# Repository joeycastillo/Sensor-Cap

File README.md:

# The Sensor Cap

Boards with a 9-pin JST-SH connector for sensors, inspired by the [Adafruit Monster M4SK](https://www.adafruit.com/product/4343).

This started as a project to mount a temperature sensor on my forehead for continuous temperature monitoring. It's ended up being something broader in nature. Call it a general platform for wearable tech and citizen science, maybe? Also as a side note, I'm hunting for a new name for this project since it's more than a hat now.

You might ask: why another board? Why not just use a Feather? The answer is that while Feathers are AWESOME, tiny and portable and battery-operated, the main method for attaching wings (board to board pin headers) makes the solution a little more bulky than I would like for something like a hat or a watch. Standards like STEMMA and STEMMA-QT address that somewhat, but STEMMA ports only break out one signal, and STEMMA-QT only supports I²C devices.

This standard breaks out three to five analog signals and I²C. It's far fewer than a Feather header offers, but still, I sense, enough to do some useful stuff! In addition, the connector is small enough that you can keep your sensor boards very small, which is great for wearables, and makes it really cheap to prototype a tiny board at OSH Park.

## Scope

This document describes a connector with a baseline of functionality for designing small PCB's with sensors. Before diving in, some nomenclature: a **main board** hosts whatever microcontroller or processor is driving gadgets on a **sensor board**.

The intent is for different main boards with different goals (i.e low power, machine learning, compact form factor, IOT) to implement this baseline level of functionality on a standard pinout, so that sensor boards know where to expect which functions.

It is not designed for daisy-chaining like STEMMA or Qwiic. When you design your sensor board, you can make use of all of the available pins, secure in the knowledge that you don't need to plan on sharing (except in the case of the I²C pins but, y'know, you can play nice with others there).

Main boards can offer additional functionality on some pins, and this document includes guidelines about what that pinout should look like. This should maximize the amount of compatibility across boards. Still, fundamentally, I imagine the user will either be able to make their sensor package work with the baseline of the spec, or they will choose a main board that works for their project and design their sensor package to match its abilities and constraints.

## Main Board

If possible, all pins should be analog inputs; if not, make sure pins 5, 6 and 9 (A2, A1 and A0) are analog capable. If you have a DAC available, put it on pin 9, A0. All IO pins are 3.3 volt logic.

### Main Board Pinout

1. Power to the sensor board, nominally 3.3 volts, can be lower but no higher.
2. Ground. 
3. Digital input or output D1. (Optional: analog input, or SPI main in/secondary out)
4. Digital input or output D0. (Optional: analog input)
5. Analog input A2 or digital in/out. (Optional: SPI main out/secondary in)
6. Analog input A1 or digital in/out. (Optional: SPI clock)
7. I²C data.
8. I²C clock.
9. Analog input A0 or digital in/out. (Optional: Analog output)

Why are some pins designated as analog and some pins designated as either digital or analog? Because if you’re in a situation where you have a limited number of pins available, this lets you know to prioritize putting your analog inputs on pins 5, 6 and 9, and your analog output (if available) on pin 9.

The main board **must** provide I²C pull-up resistors on the SCL and SDA lines; there should be no need to include them on a sensor board. The main board may (and probably should) have its own I²C devices share this bus.

The main board should try to offer interrupt capability on all pins except SCL and SDA.

If you're in a severely GPIO constrained situation and cannot offer all 7 GPIO pins, prioritize the I²C, A0, A1 and A2 pins.

## Sensor Boards

The sensor board's 9-pin connector is rotated 180° from the main board's, which means that the numbering on the sensor board is reversed. To connect the sensor board to the main board, use a 9-pin socket-to-socket JST-SH cable like the [the one Adafruit sells](https://www.adafruit.com/product/4350), or one of the following part numbers: [A09SR09SR30K51B](https://www.digikey.com/product-detail/en/jst-sales-america-inc/A09SR09SR30K51B/455-3726-ND/6708500) (2 inch), [A09SR09SR30K102B](https://www.digikey.com/product-detail/en/jst-sales-america-inc/A09SR09SR30K102B/455-3662-ND/9922212) (4 inch), [A09SR09SR30K152B](https://www.digikey.com/product-detail/en/jst-sales-america-inc/A09SR09SR30K152B/455-3722-ND/6708509) (6 inch), [A09SR09SR30K203B](https://www.digikey.com/product-detail/en/jst-sales-america-inc/A09SR09SR30K203B/455-3664-ND/9922214) (8 inch), [A09SR09SR30K254B](https://www.digikey.com/product-detail/en/jst-sales-america-inc/A09SR09SR30K254B/455-3666-ND/9922216) (10 inch) or [A09SR09SR30K305B](https://www.digikey.com/product-detail/en/jst-sales-america-inc/A09SR09SR30K305B/455-3724-ND/6708518) (12-inch).

### Baseline Sensor Board

1. Analog signal A0
2. I²C clock SCL
3. I²C data SDA
4. Analog signal A1
5. Analog signal A2
6. Digital signal D0
7. Digital signal D1
8. Ground
9. Power

Not all main boards need to support all kinds of sensor boards, but this baseline sensor board should basically always work. When designing your sensor board, a few guidelines: 

* If you’re designing a sensor board with both digital and analog signals, prioritize putting your analog signals to the main board on pins 4 and 5, A1 and A2.
* If you require an analog signal from the main board, it will be on pin 9 (A0) if available. Otherwise, you can output a third analog signal to the main board on pin 9.
* Know that pins 6 and 7 (D0 and D1) may be either digital or analog; if you have more analog signals, you can put them there, but you should double check the capabilities of the board you are pairing with.
* If you have some signals that are nice-to-have (like interrupt pins) and others that are absolutely necessary for the board to function (like a chip select line), put your most important signals on A0, A1 and A2 (see above note re: severely constrained main boards).

Those are guidelines, but there's one constraint: your sensor board **must not** treat the SCL and SDA lines as free GPIO pins, since the I²C bus may be shared with devices on the main board.

Beyond the baseline, I can imagine a few kinds of sensor boards: 

### I²C and SPI sensor board

1. SPI Chip Select 1 (CS1)
2. I²C clock (SCL)
3. I²C data (SDA)
4. SPI Clock (SCK)
5. SPI Main Out (MOSI)
6. SPI Chip Select 2 (CS2)
7. SPI Main In (MISO)
8. Ground
9. Power

### I²C sensor board with a TFT or e-paper display

1. Free Pin A0
2. I²C clock (SCL)
3. I²C data (SDA)
4. SPI Clock (SCK)
5. SPI Main Out (MOSI)
6. TFT Chip Select (CS)
7. TFT Data/Command (DC)
8. Ground
9. Power

Side note: this is already basically the MONSTER M4SK left eye! Note though that the MONSTER M4SK uses a Seesaw chip on the I²C bus to manage the TFT’s reset and backlight pins, which is to say you might need to add a GPIO expander on the I²C bus to fully realize this design.

### Fully analog sensor board

1. Analog signal (A0)
2. NC
3. NC
4. Analog signal (A1)
5. Analog signal (A2)
6. Analog signal (A3)
7. Analog signal (A4)
8. Ground
9. Power

## Existing Main Boards

I've designed two of these so far, at two very different ends of the spectrum.

### The SAMD51 Sensor Cap Mainboard

This is a zippy ARM Cortex M4 board using the SAMD51G19A. While it is not a Feather, it retains the size and shape of a Feather and the same mounting hole arrangement, so it should be broadly compatible with Feather enclosures. It even has the battery connector in the same spot. 

The board works with CircuitPython! An Arduino core is on its way, I just haven't gotten to it yet.

You might wonder, why use a whole M4 microcontroller for just a handful of signals? It does other things! And has other ports to output things based on your sensor inputs.

#### Connectivity

* One STEMMA port with current and voltage protection (I imagine using this for an external Neopixel strip)
* One STEMMA-QT port for I²C stuff (ideal for adding, say, an OLED display)
* Six pins (a spare SERCOM + two GPIO) broken out with 3.3v power and ground on a 2x4 socket header. The pins are configured as a UART and arranged to match an ESP-01 module for wifi, but I haven't tested this yet.
* Micro-USB port, of course!

#### Features

* 4 MB QSPI Flash for CircuitPython and data logging
* On-board side-view Neopixel for status and color
* Two buttons for pressing, both on interrupt pins
* A small speaker with amplifier on one of the DAC lines, for beeping and speaking
* An on-board thermistor for general temperature sensing
* Battery charging

It also has two options for a real-time clock: 

* You can add a DS3231 Extremely Accurate RTC to get extremely good timekeeping (and a programmable alarm on an interrupt pin)
* But there's also a 32768 Hz crystal for ZeroRTC, and a solder jumper to bring the battery backup power to the SAMD51's VBAT power pin. (need to check on software support for this)

The 9-pin connector supports analog signals on all pins, and the second DAC is on pin A0. Unfortunately due to pin muxing constraints, it does not support hardware SPI on pins A1, A2 and D1; you'll have to bitbang it.

Anyway! Wearable tech is an obvious use case for this board, and the SAMD51 is powerful enough to run, like, TensorFlow Lite models on the sensor data you bring in. It's a thinking cap!

### The SAMD11 Minimalist Sensor Cap

This one I'm still iterating on. The idea was to make something *incredibly* cheap and low-power for data acquisition, and the SAMD11D14AS fit the bill. Unfortunately, on initial testing, I think the coin cell I chose is too small to last more than a day or two, even with low power modes.

I think this can still work for intermittent data logging; if the device spends most of its time in shutdown mode, and only wakes up for measurement when the user hits the reset button, it might work! I need to do more testing. Either way, I might redesign this with either a bigger coin cell or contacts for an alkaline battery pack.

You can play with this board using the [MattairTech SAMD11 Core](https://github.com/mattairtech/ArduinoCore-samd), but truth be told the Arduino core is so big, it's hard to keep even a kilobyte free at the end for data logging. There's a demo sketch in the repository that does work, but I expect to have to learn to write firmware from scratch to help this board reach its full potential.

#### Connectivity

* USB-A port on the PCB. Depending on the PCB thickness you may have to add a shim underneath for good contact. 

#### Features

* On-board thermistor for temperature sensing
* LIS2DH ultra low power accelerometer with two interrupt pins broken out
* 32768 Hz crystal for the real-time clock

There is no SPI Flash chip here, but you can log data to the EEPROM emulation area of the SAMD11, which should give you from one to several kilobytes of space for data.

The use case for this board is low-cost, low-power data acquisition. I'd love to get the power consumption down to the point where it can sleep most of the time, and then wake up once an hour to gather, like, environmental conditions or soil measurements. Or it could be a DIY contact thermometer; when woken up it could get ambient temperature, then flash the LED to indicate it's ready for a forehead measurement, then log the timestamped data (and blink if fever was detected).

## Existing Sensor Boards

I've thrown a lot of things at the wall so far, but the most useful ones are: 

* Temperature, Accelerometer and Speaker
* Pulse Oximetry Test Board
* Sensor Board Breakout (useful for prototyping new sensor boards!)

Future Plans? Who knows! I'm stoked at the possibilities though.

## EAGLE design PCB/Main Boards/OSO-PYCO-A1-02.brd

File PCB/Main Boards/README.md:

# EAGLE PCB Files

There are two variants of this project. You probably came for variant A1, the SAMD51-based board. A1-02 is marked "WIP" because I'm probably going to tweak the LED's a bit; tried to get clever with a bidirectional 1206 LED, and it works, but it's friendlier with two basic green and amber 0805's. Still totally buildable as-is.

Variant B1 is an experimental low power, low cost version of the cap; it's totally functional, but still I don't recommend building it just yet.

## Sensor Candle

This is a little experiment in making a small passive device for indicating things based on sensor data. It uses a SAMD11, which is a very smol chip with only 16 kilobytes of memory! I'm still hacking on the Arduino core for it, but for now you can use the [MattairTech SAMD/L/C board support package](https://www.mattairtech.com/software/arduino/package_MattairTech_index.json). The core I'm hacking on replaces the 4kB CDC bootloader with a [1kB DFU bootloader](https://github.com/majbthrd/SAMDx1-USB-DFU-Bootloader), which frees up a lot of space for user code.

Sensor candle is simple, but there are also a lot of different options for how to build and power it:

* You can omit `J2`, the 9-pin connector, if you don't plan to use external sensor boards (you still get the on-board accelerometer and RTC).
* Of course you can also omit accelerometer U3 (as well as C9 and C10) to skip that bit of functionality too.
* You can omit `U4`, `R5`, `C7` and `C8` if you don't care about the 1.8 volt power supply (either because you skipped J2, or because you plan to power your sensor boards with VCC via the POWER_OUT solder jumper).
* While this board includes a 3.3 volt regulator (U1) for powering the device over USB or with some battery options, you can omit it completely if you plan to supply the board with a coin cell or a pair of alkaline batteries. In this case you can also omit `R5`, `C1`, `C7`, `D1` and `D2`. In this configuration, when you plug in to USB, you'll get USB data but no USB power.
* Finally, `R12`and `R13` are a voltage divider on the coin cell to monitor battery level. If you aren't using a coin cell (or don't want to lose one channel from the sensor board), you can omit R12 and R13.

In addition, you can choose what LEDs you want to use! Standard 0805 LED's with ~ 2V forward voltage will always work. You can use blue or white LED's as well, but only if you are powering your board with USB or the 4.5V pin (coin cells or a pair of AA's don't quite have the required oomph).

### Power

You can power the board one of three ways. You should ONLY choose one.

* Connect a LiPo battery pack or 3x AA cells to the 4.5V pin. This powers 3.3 volt regulator U1 for a steady 3.3 volts to your project for most of the battery's life. Note that there is no LiPo charging on board so you probably want to solder a [JST-PH cable](https://www.adafruit.com/product/3814) to these pins, so that you can unplug your battery and recharge elsewhere.
* OR connect 2x AA cells to the 3V pin. This provides 3 volts to your project when the batteries are fresh, but that will decline steadily as the batteries discharge.
* OR insert a coin cell into the coin cell holder. This will provide ~ 2.9 volts to your project when the battery is full, but that too will decline as the battery dies. It will hang above 2.7 volts for most of its usable life, but once it declines to 2.6 volts, the end is nigh.

Note that if you are using the 1.8 volt regulator as a reference and power to your sensor board, the SAMD11's ADC really wants the external reference voltage to be no more than the supply voltage minus 0.6 volts. So you really should replace your battery once it gets down to 2.4 volts.

### Peripherals and Possibilities

The 1.8 volt voltage regulator is there so that you can hang out in low power sleep mode most of the time, and only power up the sensor board for an occasional reading (say, an alarm from the RTC or an interrupt from the accelerometer). PA27 is the regulator control pin; it's pulled down by default, so you will have to set it high to power your sensor board.

The real-time clock "Just Works" with [RTCZero](https://github.com/arduino-libraries/RTCZero). Hooray!

For the LIS2DH accelerometer, you can look to most any LIS3DH library for guidance — they're compatible — but most libraries tend to include floating point math that doesn't fit in the SAMD11's program memory. I ended up using [this one](https://github.com/ldab/lis3dh-motion-detection) and replacing all references to `float` with `int`. ¯\\\_(ツ)_/¯

I'm trying to get the [Arduino FlashStorage library](https://github.com/cmaglie/FlashStorage) working with the DFU bootloader. It works with the Mattairtech CDC bootloader, but I think the checksumming of the DFU bootloader fails once I start logging data to the Flash. To be continued.

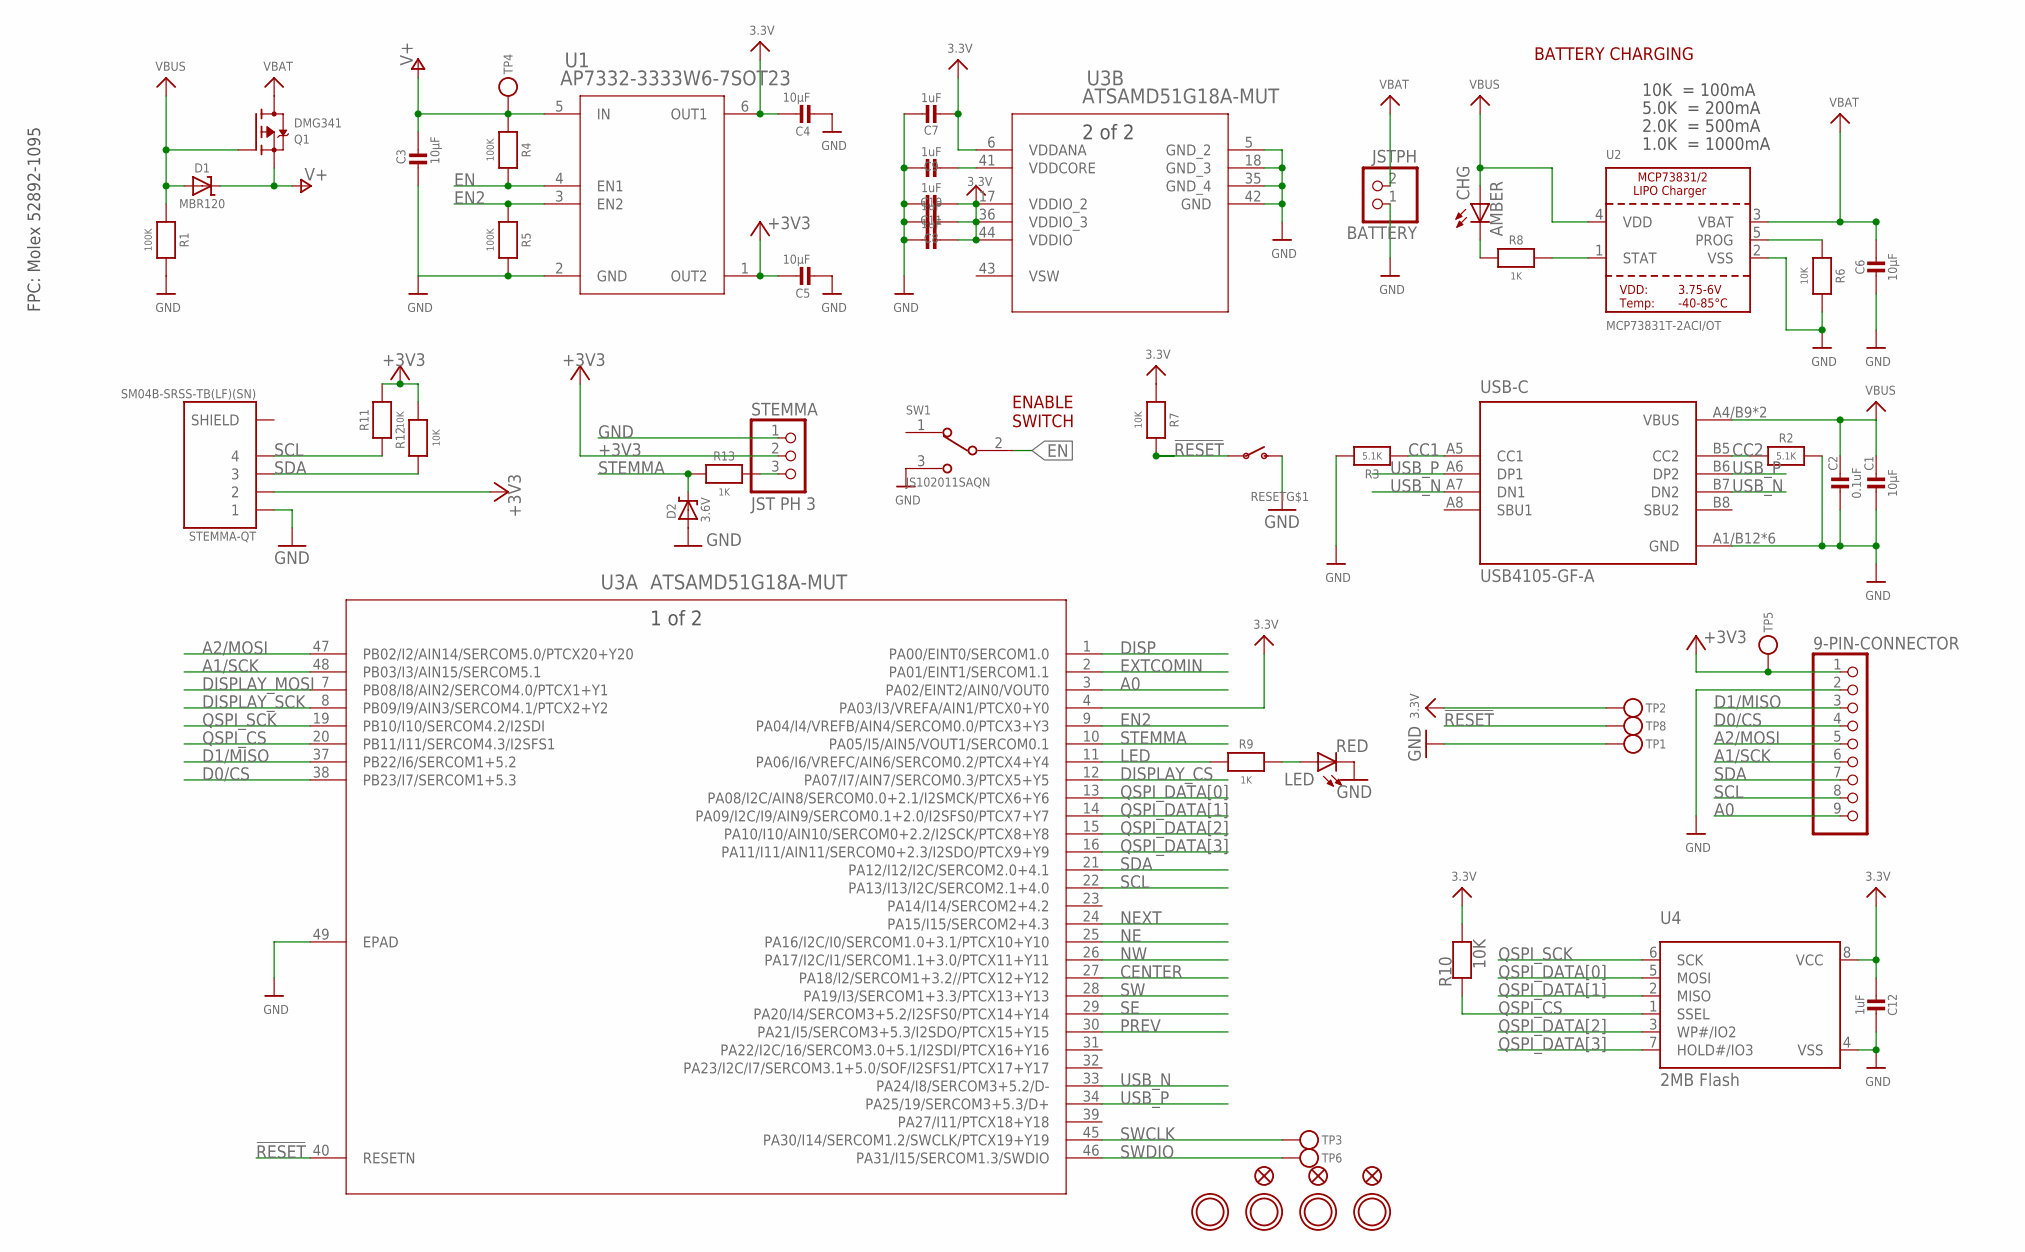
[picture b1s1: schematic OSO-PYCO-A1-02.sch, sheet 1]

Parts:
9-PIN-CONNECTOR: HEADER-1X9_JSTSH; JST_SH9
BATTERY: JSTPH; JSTPH2
C1, C3, C4, C5, C6: 10µF; 0805-NO
C2: 0.1uF; _0603MP
C7, C8, C9, C10, C11, C12: 1uF; _0603MP
CHG: AMBER; CHIP-LED0805
D1: MBR120; SOD-123
D2: 3.6V; SOD-123
FID1, FID2, FID3: FIDUCIAL_1MM
LED: RED; CHIP-LED0805
Q1: DMG341; SOT23-R
R1, R4, R5: 100K; _0603MP
R2, R3: 5.1K; _0603MP
R6, R7, R10, R11, R12: 10K; _0603MP
R8, R9, R13: 1K; _0603MP
RESET: SWITCH_SPSTTL3330A; TL3330A
STEMMA: JST PH 3; JSTPH3
STEMMA-QT: SM04B-SRSS-TB(LF)(SN); JST_SM04B-SRSS-TB(LF)(SN)
SW1: JS102011SAQN; SW_JS102011SAQN
TP1, TP2, TP3, TP4, TP5, TP6, TP8: TESTPOINTROUND2MMNO; TESTPOINT_ROUND_2MM_NO
U1: AP7332-3333W6-7SOT23; SOT23-6
U2: MCP73831T-2ACI/OT; SOT23-5
U3: ATSAMD51G18A-MUT; QFN48_7X7MC
U4: 2MB Flash; SOIC8_150MIL
U$9, U$10, U$27, U$28: MOUNTINGHOLE2.5; MOUNTINGHOLE_2.5_PLATED
USB-C: USB4105-GF-A; GCT_USB4105-GF-A

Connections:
3.3V: C4.1, C7.2, C8.2, C10.2, C11.2, C12.2, R7.1, R10.2, TP2.P$1, U1.6 (OUT1), U3.4 (PA03/I3/VREFA/AIN1/PTCX0+Y0), U3.6 (VDDANA), U3.17 (VDDIO_2), U3.36 (VDDIO_3), U3.44 (VDDIO), U4.8 (VCC); also elsewhere on the board
!RESET: R7.2, RESET.P$1, TP8.P$1, U3.40 (RESETN)
+3V3: 9-PIN-CONNECTOR.1, C5.1, R11.2, R12.2, STEMMA.2, STEMMA-QT.2, TP5.P$1, U1.1 (OUT2)
A0: 9-PIN-CONNECTOR.9, U3.3 (PA02/EINT2/AIN0/VOUT0)
A1/SCK: 9-PIN-CONNECTOR.6, U3.48 (PB03/I3/AIN15/SERCOM5.1)
A2/MOSI: 9-PIN-CONNECTOR.5, U3.47 (PB02/I2/AIN14/SERCOM5.0/PTCX20+Y20)
CC1: R3.1, USB-C.A5 (CC1)
CC2: R2.1, USB-C.B5 (CC2)
CENTER: U3.27 (PA18/I2/SERCOM1+3.2//PTCX12+Y12); also elsewhere on the board
D0/CS: 9-PIN-CONNECTOR.4, U3.38 (PB23/I7/SERCOM1+5.3)
D1/MISO: 9-PIN-CONNECTOR.3, U3.37 (PB22/I6/SERCOM1+5.2)
DISP: U3.1 (PA00/EINT0/SERCOM1.0); also elsewhere on the board
DISPLAY_CS: U3.12 (PA07/I7/AIN7/SERCOM0.3/PTCX5+Y5); also elsewhere on the board
DISPLAY_MOSI: U3.7 (PB08/I8/AIN2/SERCOM4.0/PTCX1+Y1); also elsewhere on the board
DISPLAY_SCK: U3.8 (PB09/I9/AIN3/SERCOM4.1/PTCX2+Y2); also elsewhere on the board
EN: R4.2, SW1.2, U1.4 (EN1); also elsewhere on the board
EN2: R5.1, U1.3 (EN2), U3.9 (PA04/I4/VREFB/AIN4/SERCOM0.0/PTCX3+Y3)
EXTCOMIN: U3.2 (PA01/EINT1/SERCOM1.1); also elsewhere on the board
GND: 9-PIN-CONNECTOR.2, BATTERY.1, C1.2, C2.2, C3.2, C4.2, C5.2, C6.2, C7.1, C8.1, C9.1, C10.1, C11.1, C12.1, D2.A, LED.C, R1.2, R2.2, R3.2, R5.2, R6.2, RESET.P$2 (S), STEMMA.1, STEMMA-QT.1, SW1.3, TP1.P$1, U1.2 (GND), U2.2 (VSS), U3.5 (GND_2), U3.18 (GND_3), U3.35 (GND_4), U3.42 (GND), U3.49 (EPAD), U4.4 (VSS), USB-C.A1/B12 (GND), USB-C.B1/A12 (GND), USB-C.G1 (GND), USB-C.G2 (GND), USB-C.G3 (GND), USB-C.G4 (GND); also elsewhere on the board
LED: R9.1, U3.11 (PA06/I6/VREFC/AIN6/SERCOM0.2/PTCX4+Y4)
unnamed: LED.A, R9.2
unnamed: CHG.C, R8.1
NE: U3.25 (PA16/I2C/I0/SERCOM1.0+3.1/PTCX10+Y10); also elsewhere on the board
NEXT: U3.24 (PA15/I15/SERCOM2+4.3); also elsewhere on the board
NW: U3.26 (PA17/I2C/I1/SERCOM1.1+3.0/PTCX11+Y11); also elsewhere on the board
PREV: U3.30 (PA21/I5/SERCOM3+5.3/I2SDO/PTCX15+Y15); also elsewhere on the board
PROG: R6.1, U2.5 (PROG)
QSPI_CS: R10.1, U3.20 (PB11/I11/SERCOM4.3/I2SFS1), U4.1 (SSEL)
QSPI_DATA[0]: U3.13 (PA08/I2C/AIN8/SERCOM0.0+2.1/I2SMCK/PTCX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), U4.5 (MOSI)
QSPI_DATA[1]: U3.14 (PA09/I2C/I9/AIN9/SERCOM0.1+2.0/I2SFS0/P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), U4.2 (MISO)
QSPI_DATA[2]: U3.15 (PA10/I10/AIN10/SERCOM0+2.2/I2SCK/PTCX8+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), U4.3 (WP#/IO2)
QSPI_DATA[3]: U3.16 (PA11/I11/AIN11/SERCOM0+2.3/I2SDO/PTCX9+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), U4.7 (HOLD#/IO3)
QSPI_SCK: U3.19 (PB10/I10/SERCOM4.2/I2SDI), U4.6 (SCK)
SCL: 9-PIN-CONNECTOR.8, R11.1, STEMMA-QT.4, U3.22 (PA13/I13/I2C/SERCOM2.1+4.0)
SDA: 9-PIN-CONNECTOR.7, R12.1, STEMMA-QT.3, U3.21 (PA12/I12/I2C/SERCOM2.0+4.1)
SE: U3.29 (PA20/I4/SERCOM3+5.2/I2SFS0/PTCX14+Y14); also elsewhere on the board
STAT: R8.2, U2.1 (STAT)
STEMMA: D2.C, R13.2, U3.10 (PA05/I5/AIN5/VOUT1/SERCOM0.1)
STEMMA_: R13.1, STEMMA.3
SW: U3.28 (PA19/I3/SERCOM1+3.3/PTCX13+Y13); also elsewhere on the board
SWCLK: TP3.P$1, U3.45 (PA30/I14/SERCOM1.2/SWCLK/PTCX19+Y19)
SWDIO: TP6.P$1, U3.46 (PA31/I15/SERCOM1.3/SWDIO)
USB_N: U3.33 (PA24/I8/SERCOM3+5.2/D-), USB-C.A7 (DN1), USB-C.B7 (DN2)
USB_P: U3.34 (PA25/19/SERCOM3+5.3/D+), USB-C.A6 (DP1), USB-C.B6 (DP2)
V+: C3.1, D1.C, Q1.2 (S), R4.1, TP4.P$1, U1.5 (IN); also elsewhere on the board
VBAT: BATTERY.2, C6.1, Q1.3 (D), U2.3 (VBAT)
VBUS: C1.1, C2.1, CHG.A, D1.A, Q1.1 (G), R1.1, U2.4 (VDD), USB-C.A4/B9 (VBUS), USB-C.B4/A9 (VBUS)
VDDCORE1: C9.2, U3.41 (VDDCORE)
VSW: U3.43 (VSW)

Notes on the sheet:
FPC: Molex 52892-1095
ENABLE SWITCH
10K = 100mA
5.0K = 200mA
2.0K = 500mA
1.0K = 1000mA
BATTERY CHARGING

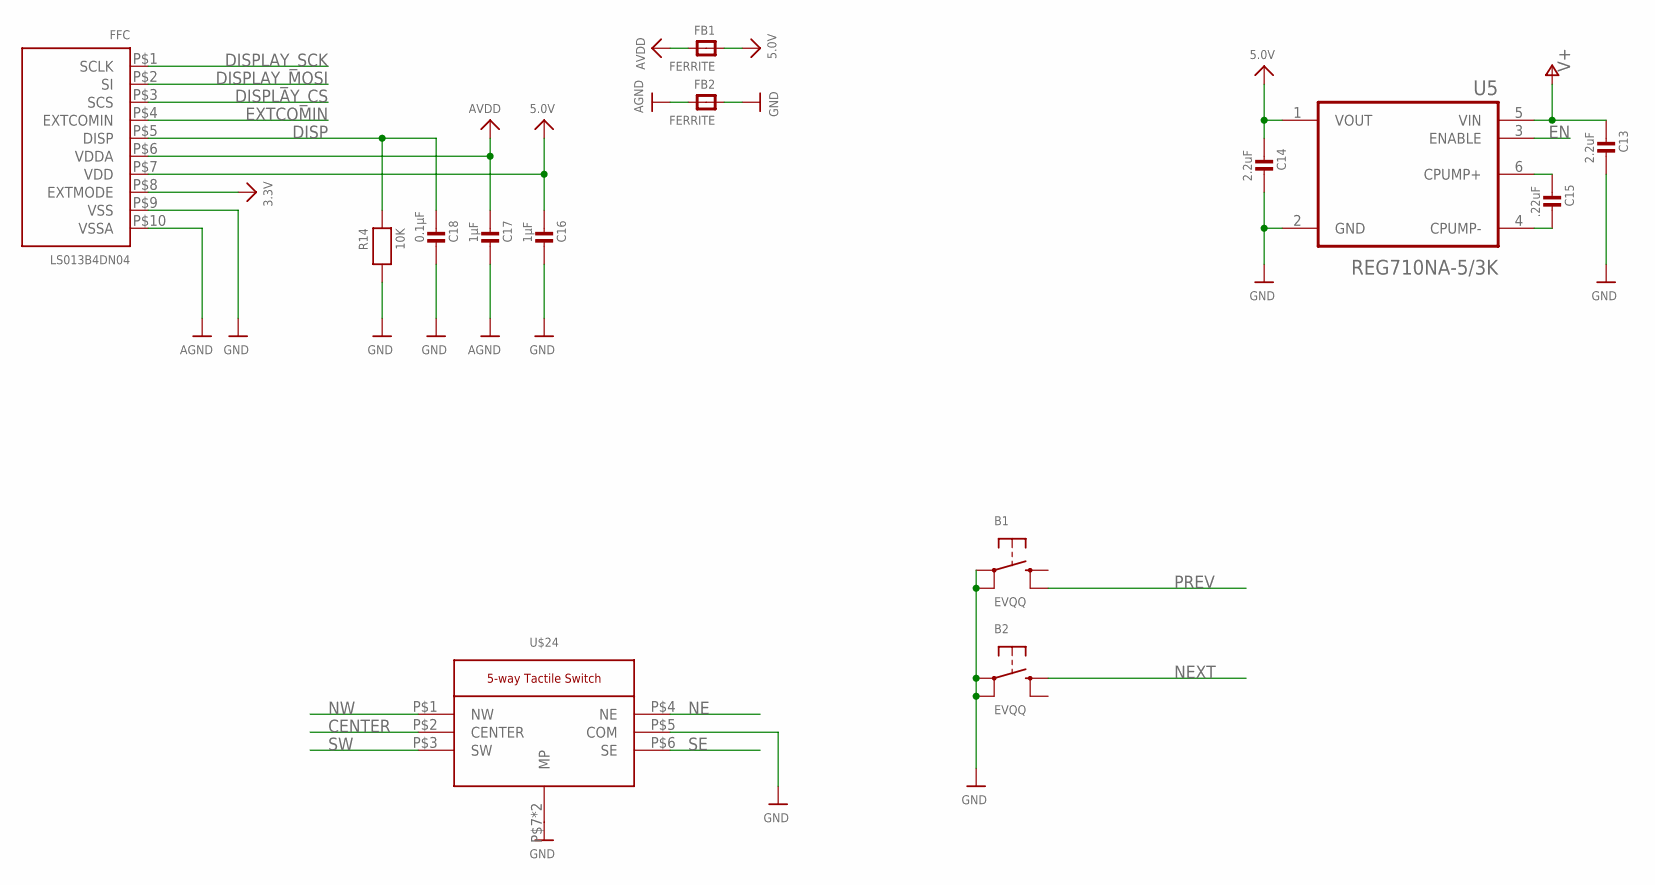
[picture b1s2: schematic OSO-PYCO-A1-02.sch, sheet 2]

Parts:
B1, B2: EVQQ; 6MMX6MM_TACTILE_SMT
C13, C14: 2.2uF; _0603MP
C15: .22uF; _0603MP
C16, C17: 1µF; _0603MP
C18: 0.1µF; _0603MP
FB1, FB2: FERRITE; _0805
FFC: LS013B4DN04; SHARP_2.7IN
R14: 10K; _0603MP
U5: REG710NA-5/3K; SOT95P280X145-6N
U$24: K1-5202UA

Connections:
3.3V: FFC.P$8 (EXTMODE); also elsewhere on the board
5.0V: C14.1, C16.1, FB1.1, FFC.P$7 (VDD), U5.1 (VOUT)
AGND: C17.2, FB2.2, FFC.P$10 (VSSA)
AVDD: C17.1, FB1.2, FFC.P$6 (VDDA)
CENTER: U$24.P$2 (CENTER); also elsewhere on the board
DISP: C18.1, FFC.P$5 (DISP), R14.1; also elsewhere on the board
DISPLAY_CS: FFC.P$3 (SCS); also elsewhere on the board
DISPLAY_MOSI: FFC.P$2 (SI); also elsewhere on the board
DISPLAY_SCK: FFC.P$1 (SCLK); also elsewhere on the board
EN: U5.3 (ENABLE); also elsewhere on the board
EXTCOMIN: FFC.P$4 (EXTCOMIN); also elsewhere on the board
GND: B1.A, B1.A' (P1), B2.A, B2.A' (P1), C13.2, C14.2, C16.2, C18.2, FB2.1, FFC.P$9 (VSS), R14.2, U5.2 (GND), U$24.P$5 (COM), U$24.P$7 (MP), U$24.P$8 (MP); also elsewhere on the board
unnamed: C15.1, U5.6 (CPUMP+)
unnamed: C15.2, U5.4 (CPUMP-)
NE: U$24.P$4 (NE); also elsewhere on the board
NEXT: B2.B (S); also elsewhere on the board
NW: U$24.P$1 (NW); also elsewhere on the board
PREV: B1.B' (S1); also elsewhere on the board
SE: U$24.P$6 (SE); also elsewhere on the board
SW: U$24.P$3 (SW); also elsewhere on the board
V+: C13.1, U5.5 (VIN); also elsewhere on the board

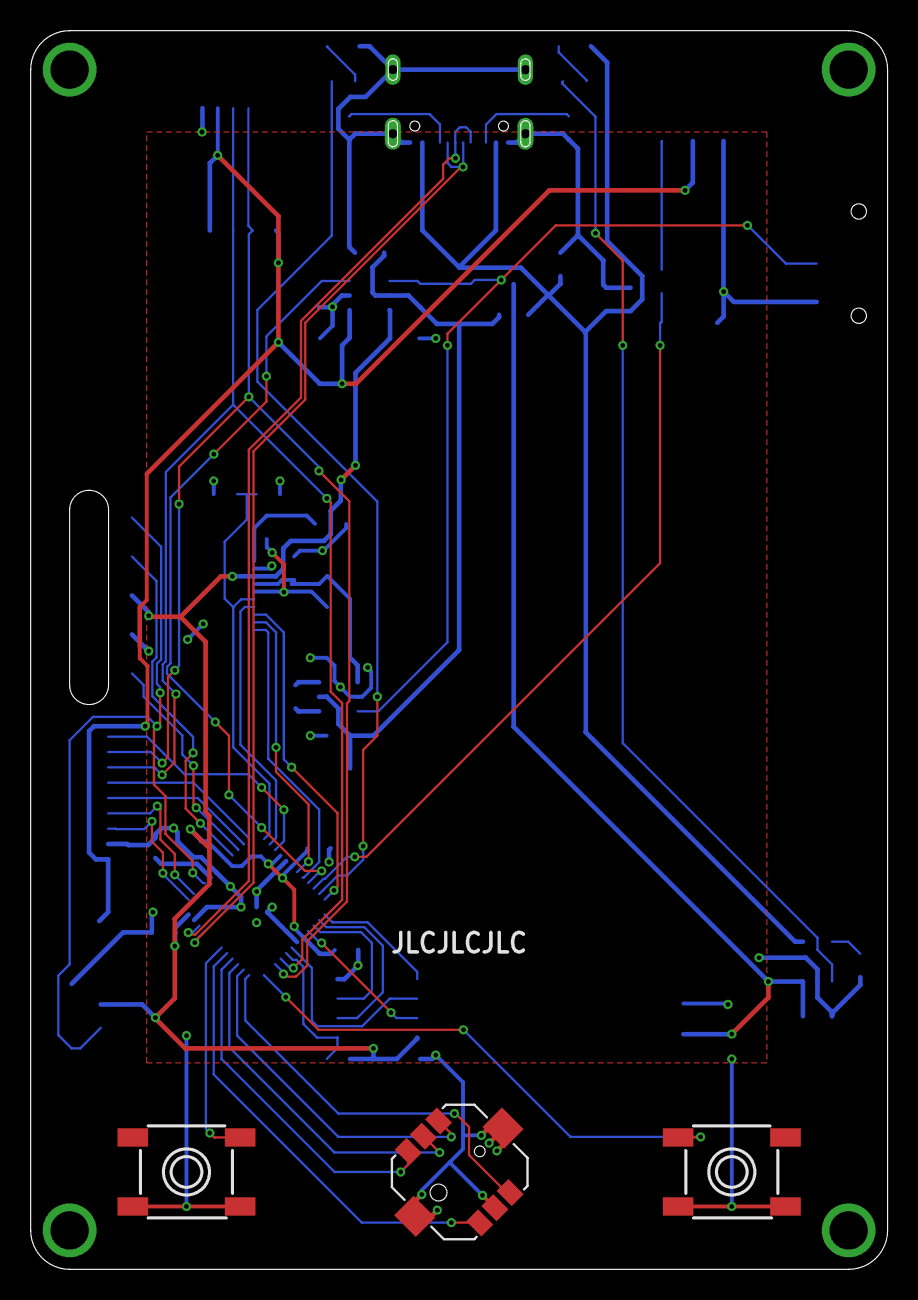
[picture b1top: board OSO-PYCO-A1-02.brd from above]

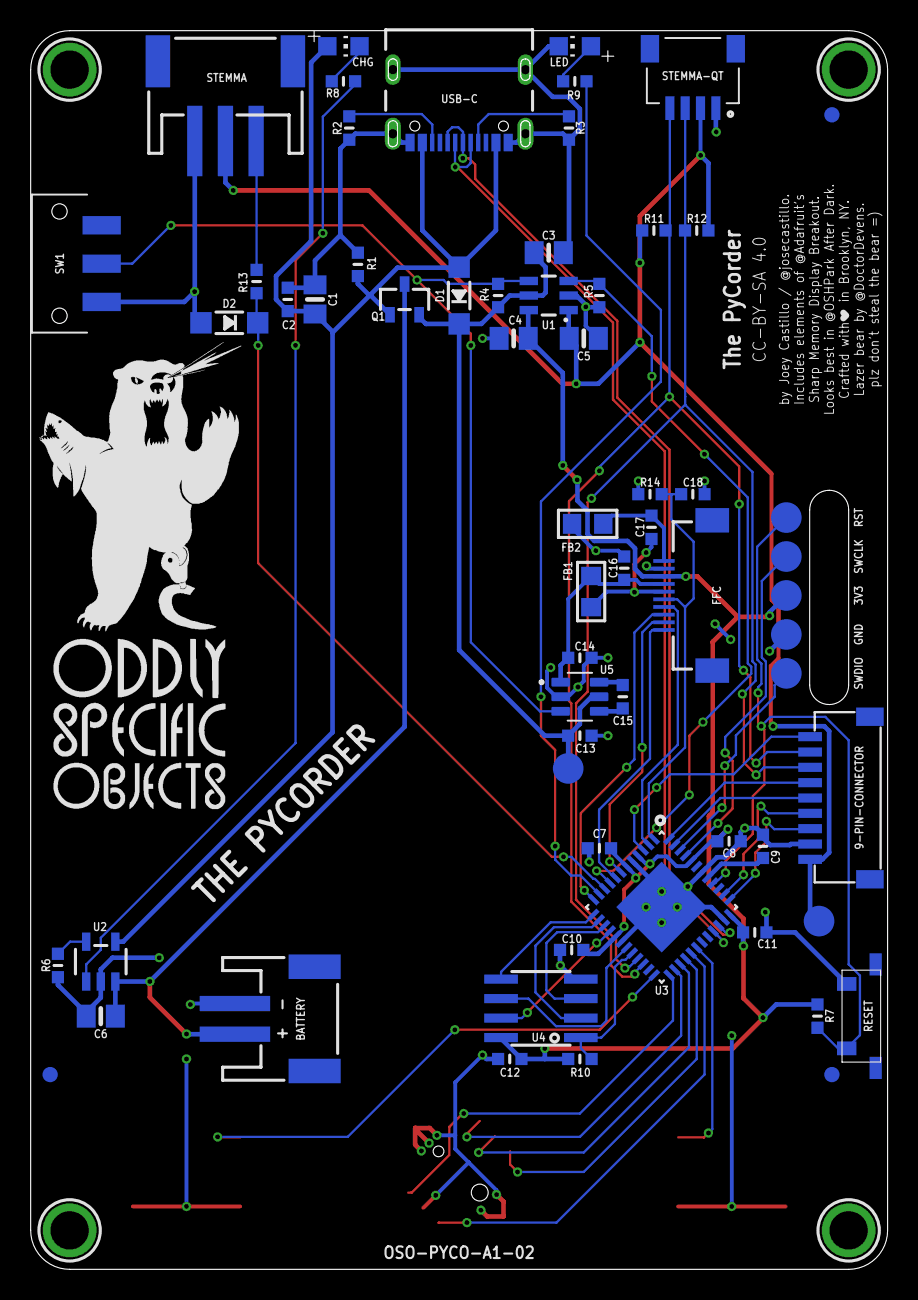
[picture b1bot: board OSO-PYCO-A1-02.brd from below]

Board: 2 copper layers, 55.9 x 80.8 mm, 71 parts (68 on the bottom side), 53 nets.

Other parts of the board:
U$16: OSO_WORDMARK_THREELINE_450MIL_1000DPI
U$67: OSO_BEAR_525X750MIL_1000DPI

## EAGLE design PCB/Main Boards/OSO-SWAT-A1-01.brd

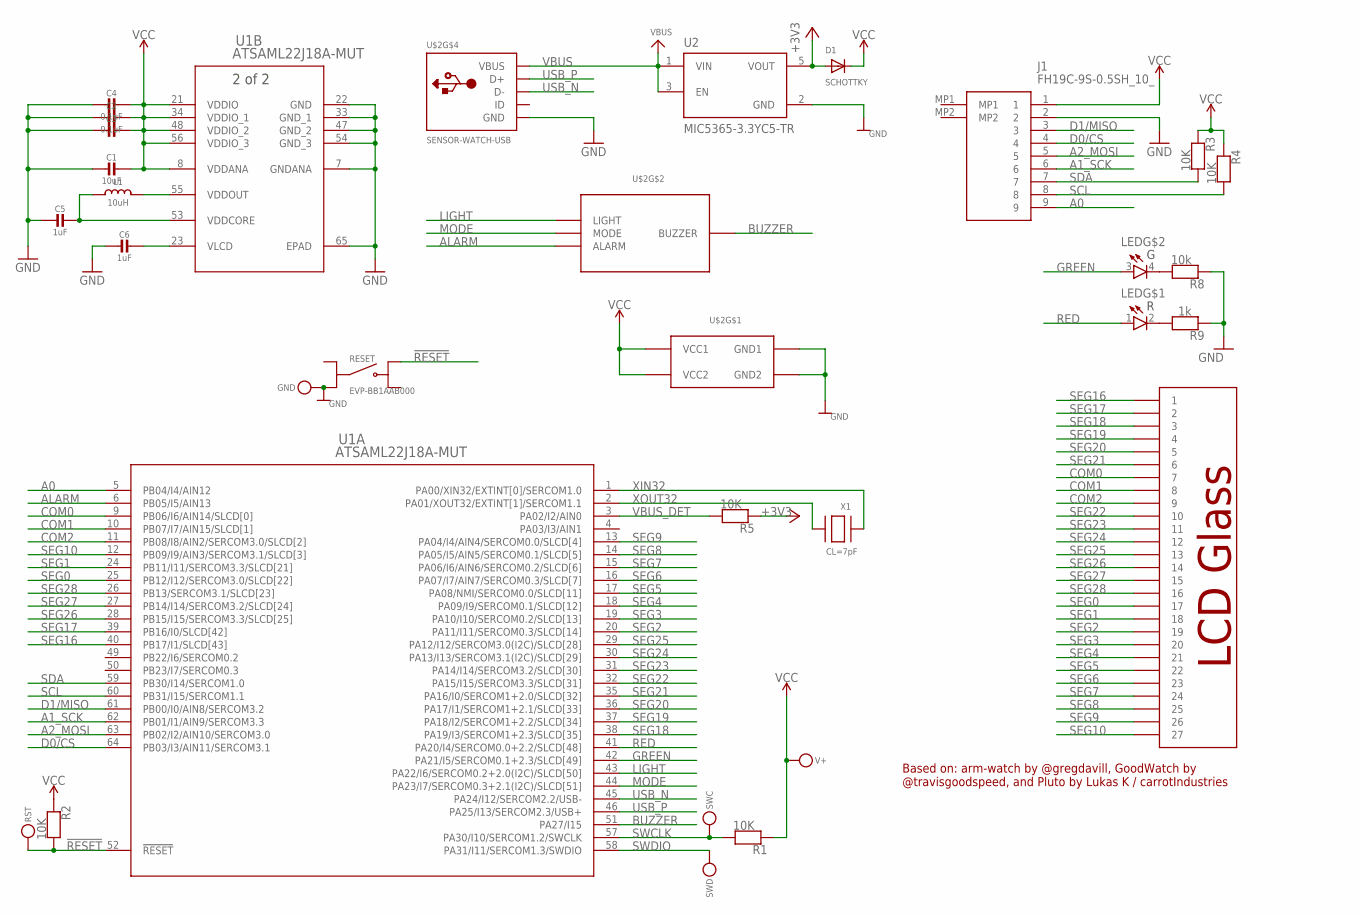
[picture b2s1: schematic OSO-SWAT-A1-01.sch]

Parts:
C1: 10uF; _0603MP
C2, C3, C4: 0.1uF; _0603MP
C5, C6: 1uF; _0603MP
D1: SCHOTTKY; SOD-323F
GND: MICROBUILDER_TESTPOINTROUND1.5MM; MICROBUILDER_TESTPOINT_ROUND_1.5MM
J1: FH19C-9S-0.5SH_10_; FH19C9S05SH10
L1: 10uH; MICROBUILDER__0805MP
LED: QBLP655R; LED_QBLP655R
R1, R2, R3, R4, R5: 10K; _0603MP
R8: 10k; _0603MP
R9: 1k; _0603MP
RESET: EVP-BB1AAB000; SW_EVP-BB1AAB000
RST: MICROBUILDER_TESTPOINTROUND1.5MM; MICROBUILDER_TESTPOINT_ROUND_1.5MM
SWC: MICROBUILDER_TESTPOINTROUND1.5MM; MICROBUILDER_TESTPOINT_ROUND_1.5MM
SWD: MICROBUILDER_TESTPOINTROUND1.5MM; MICROBUILDER_TESTPOINT_ROUND_1.5MM
U1: ATSAML22J18A-MUT; QFN64_9X9MC_MCH
U2: MIC5365-3.3YC5-TR; SOT65P210X110-5N
U$2: SENSOR-WATCH-USB; CASIO-F91W-OUTLINE-USB
V+: MICROBUILDER_TESTPOINTROUND1.5MM; MICROBUILDER_TESTPOINT_ROUND_1.5MM
X1: CL=7pF; XTAL3215

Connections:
!RESET: R2.2, RESET.B1, RST.P$1, U1.52 (!RESET)
+3V3: D1.A, R5.1, U2.5 (VOUT)
A0: J1.9, U1.5 (PB04/I4/AIN12)
A1_SCK: J1.6, U1.62 (PB01/I1/AIN9/SERCOM3.3)
A2_MOSI: J1.5, U1.63 (PB02/I2/AIN10/SERCOM3.0)
ALARM: U1.6 (PB05/I5/AIN13), U$2.ALARM
BUZZER: U1.51 (PA27/I15), U$2.BUZZER
COM0: U1.9 (PB06/I6/AIN14/SLCD[0]), U$2.7
COM1: U1.10 (PB07/I7/AIN15/SLCD[1]), U$2.8
COM2: U1.11 (PB08/I8/AIN2/SERCOM3.0/SLCD[2]), U$2.9
D0/CS: J1.4, U1.64 (PB03/I3/AIN11/SERCOM3.1)
D1/MISO: J1.3, U1.61 (PB00/I0/AIN8/SERCOM3.2)
GND: C1.2, C2.2, C3.2, C4.2, C5.2, C6.2, GND.P$1, J1.2, R8.1, R9.1, RESET.A2, U1.7 (GNDANA), U1.22 (GND), U1.33 (GND_1), U1.47 (GND_2), U1.54 (GND_3), U1.65 (EPAD), U2.2 (GND), U$2.GND, U$2.GND1, U$2.GND2
GREEN: LED.3 (A), U1.42 (PA21/I5/SERCOM0.1+2.3/SLCD[49])
LIGHT: U1.43 (PA22/I6/SERCOM0.2+2.0(I2C)/SLCD[50]), U$2.LIGHT
MODE: U1.44 (PA23/I7/SERCOM0.3+2.1(I2C)/SLCD[51]), U$2.MODE
unnamed: LED.4 (C), R8.2
unnamed: LED.2 (C), R9.2
RED: LED.1 (A), U1.41 (PA20/I4/SERCOM0.0+2.2/SLCD[48])
SCL: J1.8, R4.2, U1.60 (PB31/I15/SERCOM1.1)
SDA: J1.7, R3.2, U1.59 (PB30/I14/SERCOM1.0)
SEG0: U1.25 (PB12/I12/SERCOM3.0/SLCD[22]), U$2.17
SEG1: U1.24 (PB11/I11/SERCOM3.3/SLCD[21]), U$2.18
SEG2: U1.20 (PA11/I11/SERCOM0.3/SLCD[14]), U$2.19
SEG3: U1.19 (PA10/I10/SERCOM0.2/SLCD[13]), U$2.20
SEG4: U1.18 (PA09/I9/SERCOM0.1/SLCD[12]), U$2.21
SEG5: U1.17 (PA08/NMI/SERCOM0.0/SLCD[11]), U$2.22
SEG6: U1.16 (PA07/I7/AIN7/SERCOM0.3/SLCD[7]), U$2.23
SEG7: U1.15 (PA06/I6/AIN6/SERCOM0.2/SLCD[6]), U$2.24
SEG8: U1.14 (PA05/I5/AIN5/SERCOM0.1/SLCD[5]), U$2.25
SEG9: U1.13 (PA04/I4/AIN4/SERCOM0.0/SLCD[4]), U$2.26
SEG10: U1.12 (PB09/I9/AIN3/SERCOM3.1/SLCD[3]), U$2.27
SEG16: U1.40 (PB17/I1/SLCD[43]), U$2.1
SEG17: U1.39 (PB16/I0/SLCD[42]), U$2.2
SEG18: U1.38 (PA19/I3/SERCOM1+2.3/SLCD[35]), U$2.3
SEG19: U1.37 (PA18/I2/SERCOM1+2.2/SLCD[34]), U$2.4
SEG20: U1.36 (PA17/I1/SERCOM1+2.1/SLCD[33]), U$2.5
SEG21: U1.35 (PA16/I0/SERCOM1+2.0/SLCD[32]), U$2.6
SEG22: U1.32 (PA15/I15/SERCOM3.3/SLCD[31]), U$2.10
SEG23: U1.31 (PA14/I14/SERCOM3.2/SLCD[30]), U$2.11
SEG24: U1.30 (PA13/I13/SERCOM3.1(I2C)/SLCD[29]), U$2.12
SEG25: U1.29 (PA12/I12/SERCOM3.0(I2C)/SLCD[28]), U$2.13
SEG26: U1.28 (PB15/I15/SERCOM3.3/SLCD[25]), U$2.14
SEG27: U1.27 (PB14/I14/SERCOM3.2/SLCD[24]), U$2.15
SEG28: U1.26 (PB13/SERCOM3.1/SLCD[23]), U$2.16
SWCLK: R1.2, SWC.P$1, U1.57 (PA30/I10/SERCOM1.2/SWCLK)
SWDIO: SWD.P$1, U1.58 (PA31/I11/SERCOM1.3/SWDIO)
USB_N: U1.45 (PA24/I12/SERCOM2.2/USB-), U$2.USB_N (D-)
USB_P: U1.46 (PA25/I13/SERCOM2.3/USB+), U$2.USB_P (D+)
VBUS: U2.1 (VIN), U2.3 (EN), U$2.VBUS
VBUS_DET: R5.2, U1.3 (PA02/I2/AIN0)
VCC: C1.1, C2.1, C3.1, C4.1, D1.C, J1.1, R1.1, R2.1, R3.1, R4.1, U1.8 (VDDANA), U1.21 (VDDIO), U1.34 (VDDIO_1), U1.48 (VDDIO_2), U1.56 (VDDIO_3), U$2.VCC1, U$2.VCC2, V+.P$1
VDDCORE: C5.1, L1.1, U1.53 (VDDCORE)
VDDOUT: L1.2, U1.55 (VDDOUT)
VLCD: C6.1, U1.23 (VLCD)
XIN32: U1.1 (PA00/XIN32/EXTINT[0]/SERCOM1.0), X1.P$1
XOUT32: U1.2 (PA01/XOUT32/EXTINT[1]/SERCOM1.1), X1.P$2

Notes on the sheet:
Based on: arm-watch by @gregdavill, GoodWatch by @travisgoodspeed, and Pluto by Lukas K / carrotIndustries

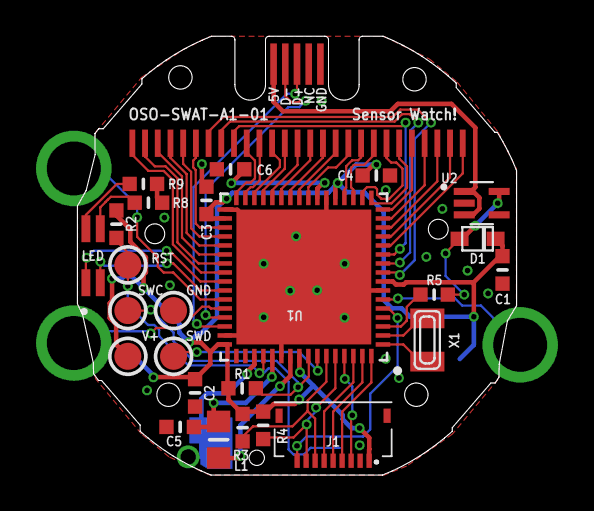
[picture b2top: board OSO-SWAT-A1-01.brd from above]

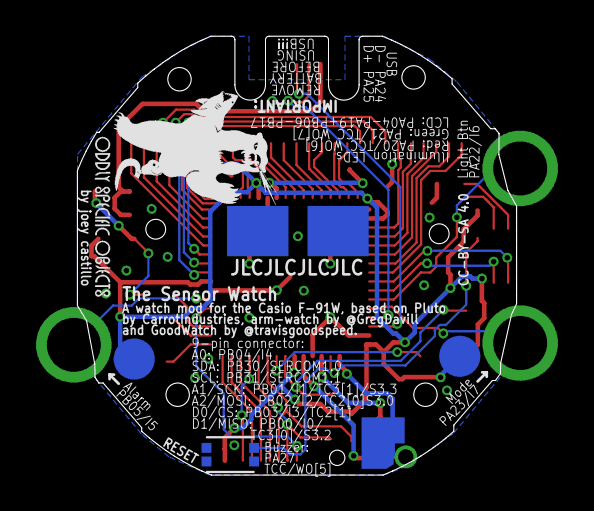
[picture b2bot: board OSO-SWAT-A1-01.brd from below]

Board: 2 copper layers, 24.4 x 24.4 mm, 29 parts (3 on the bottom side), 57 nets.

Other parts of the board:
U$5: OSO_BEAR_250X360MIL_1000DPI
U$6: OSO_WORDMARK_ONELINE_350MIL_1000DPI

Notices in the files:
PCB/Main Boards/OSO-PYCO-A1-02.brd:
CC-BY-SA 4.0
PCB/Main Boards/OSO-SWAT-A1-00.brd:
CC-BY-SA 4.0, except the bear.
PCB/Misc/OSO-MISC-20-024 Ring USB Adapter.brd:
by joey castillo. CC-BY-SA 4.0
parts and their libraries:
COPYRIGHT: Copyright (C) 2018 Accelerated Designs. All rights reserved
microbuilder: This work is placed in the public domain, and may be freely used for commercial and non-commercial work with the following conditions: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
